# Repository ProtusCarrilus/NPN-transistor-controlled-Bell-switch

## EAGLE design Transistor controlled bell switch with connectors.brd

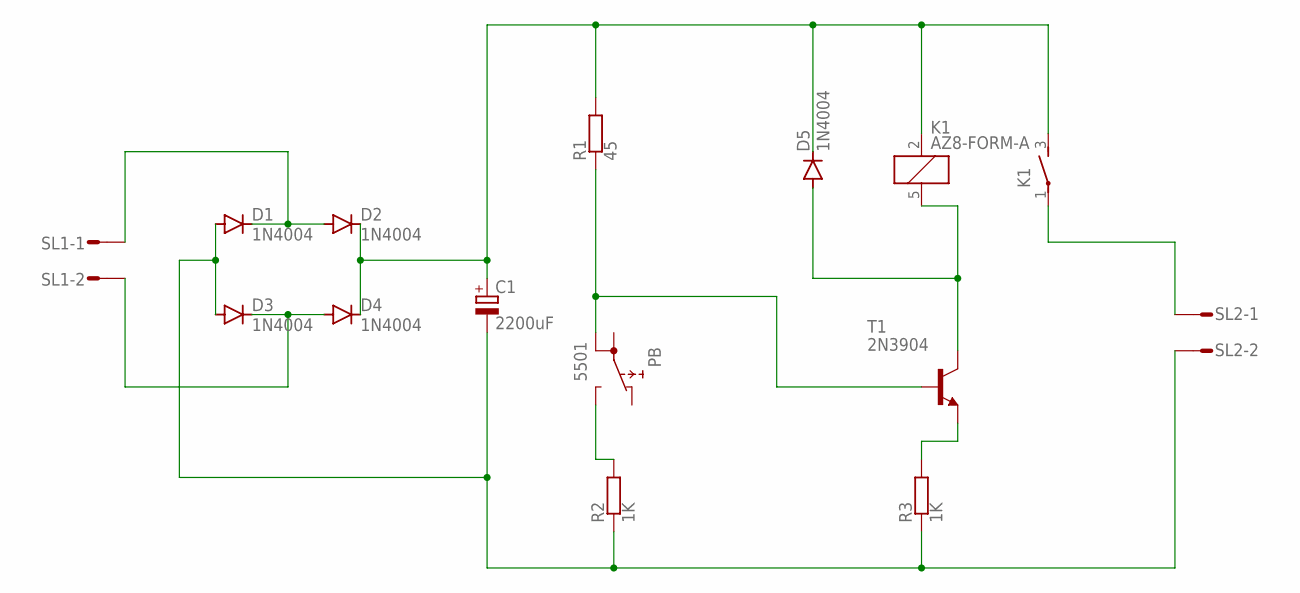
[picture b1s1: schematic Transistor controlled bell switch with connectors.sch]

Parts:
C1: 2200uF; 085CS_1AR
D1, D2, D3, D4, D5: 1N4004; DO41-10
K1: AZ8-FORM-A; AZ8
PB: 5501
R1: 45; PMD
R2, R3: 1K; PMD
SL1, SL2: M02S; 02P
T1: 2N3904; TO92

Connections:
unnamed: D1.C, D2.A, SL1.1
unnamed: PB.NO, R2.1
unnamed: D3.C, D4.A, SL1.2
unnamed: PB.1B, R1.2, T1.2 (B)
unnamed: C1.-, D1.A, D3.A, R2.2, R3.2, SL2.2
unnamed: C1.+, D2.C, D4.C, D5.C, K1.2 (1), K1.3 (S), R1.1
unnamed: R3.1, T1.3 (E)
unnamed: D5.A, K1.5 (2), T1.1 (C)
unnamed: K1.1, SL2.1

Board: 2 copper layers, 14 parts (0 on the bottom side), 9 nets, no tracks yet.
